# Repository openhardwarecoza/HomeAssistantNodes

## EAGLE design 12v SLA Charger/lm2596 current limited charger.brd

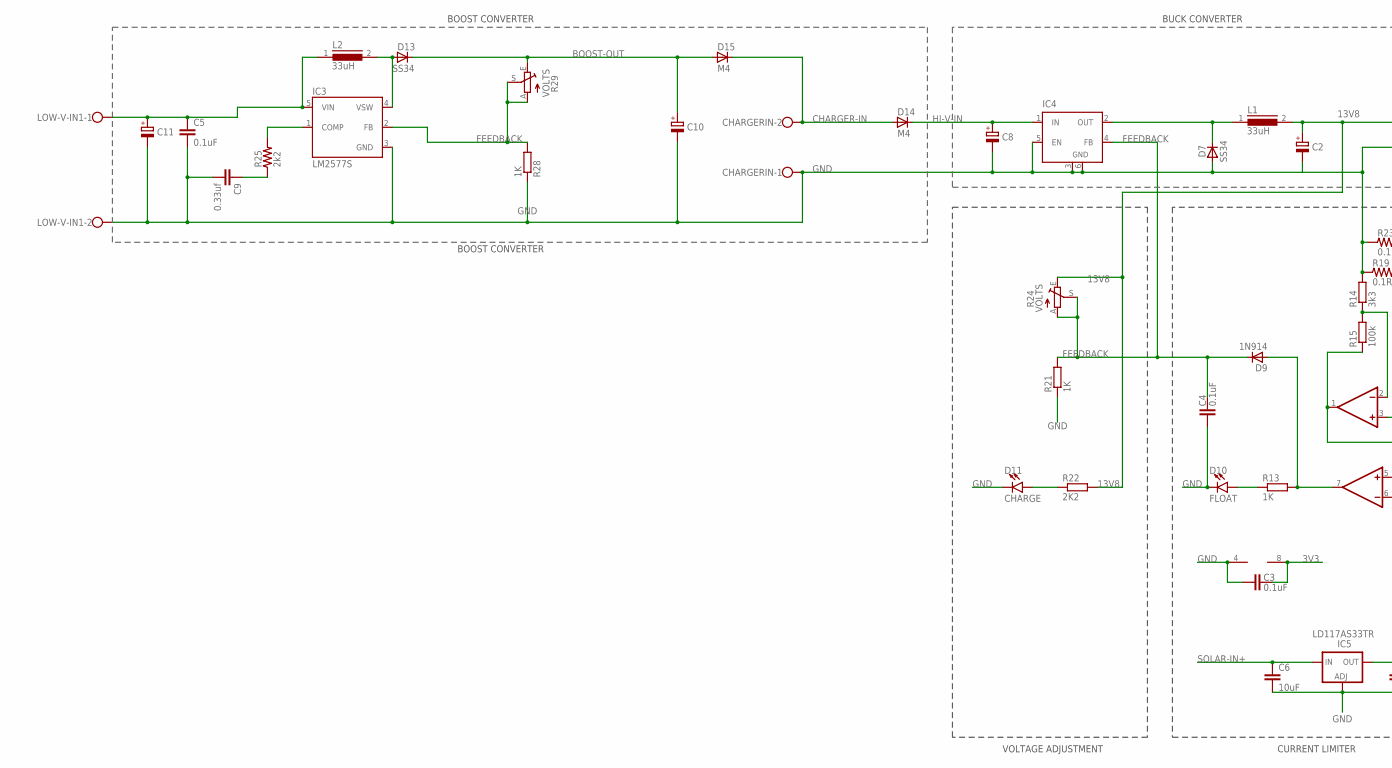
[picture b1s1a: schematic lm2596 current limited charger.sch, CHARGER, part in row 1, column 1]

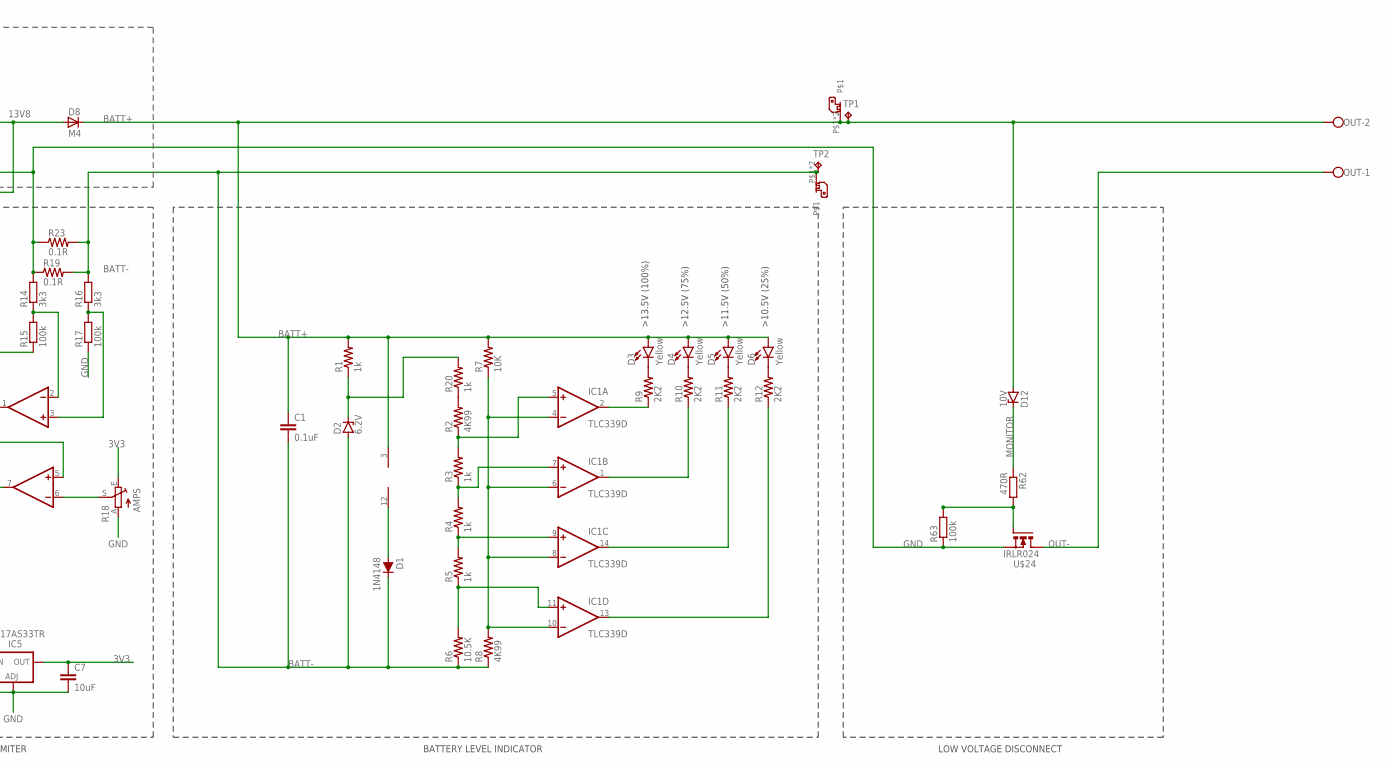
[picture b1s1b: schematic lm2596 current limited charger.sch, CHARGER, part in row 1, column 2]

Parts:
C1, C3, C4, C5: 0.1uF; C1206K
C2, C8, C10, C11: CPOL-EUE3.5-8; E3,5-8
C6, C7: 10uF; C1206K
C9: 0.33uf; C1206K
CHARGERIN: W237-102
D1: 1N4148; SOD-323
D2: 6.2V; SMB
D3, D4, D5, D6: Yellow; LED-1206
D7, D13: SS34; SOD87
D8, D14, D15: M4; SOD87
D9: 1N914; SOD87
D10: FLOAT; LED-1206
D11: CHARGE; LED-1206
D12: 10V; SMB
IC1: TLC339D; SO14
IC2: MCP602SN; SO08
IC3: LM2577S; TO263-5
IC4: LM2596S; TO263-5
IC5: LD117AS33TR; SOT223
L1, L2: 33uH; DR127
LOW-V-IN1: W237-102
OUT: W237-102
R1, R3, R4, R5, R20: 1k; R1206
R2, R8: 4K99; R1206
R6: 10.5K; R1206
R7: 10K; R1206
R9, R10, R11, R12, R22: 2K2; R1206
R13, R21, R28: 1K; R1206
R14, R16: 3k3; R1206
R15, R17: 100k; R1206
R18: AMPS; B64Y
R19, R23: 0.1R; R2512
R24, R29: VOLTS; B64Y
R25: 2k2; R2512
R62: 470R; R0603
R63: 100k; R0603
TP1, TP2: TPPAD1-20Y; P1-20Y
U$2, U$3: PCB-6.35MM-RA-SPADE
U$24: IRLR024; D-PAK_TO252AA

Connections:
3V3: C3.2, C7.1, IC2.8 (V+), IC5.4 (OUT), R18.E
13V8: C2.+, D8.2 (A), L1.2, R22.2, R24.E
BATT+: C1.1, D3.A, D4.A, D5.A, D6.A, D8.1 (C), D12.A, IC1.3 (V+), OUT.2, R1.2, R7.2, TP1.TP, U$2.P$1, U$2.P$2
BATT-: C1.2, D1.C, D2.A, R6.1, R8.1, R16.2, R19.2, R23.2, TP2.TP, U$3.P$1, U$3.P$2
BOOST-OUT: C10.+, D13.1 (C), D15.2 (A), R29.E
CHARGER-IN: CHARGERIN.2, D14.2 (A), D15.1 (C)
FEEDBACK: C4.2, D9.1 (C), IC3.2 (FB), IC4.4 (FB), R21.2, R24.A, R24.S, R28.2, R29.A, R29.S
GND: C2.-, C3.1, C4.1, C5.2, C6.2, C7.2, C8.-, C9.2, C10.-, C11.-, CHARGERIN.1, D7.2 (A), D10.C, D11.C, IC2.4 (V-), IC3.3 (GND), IC4.3 (GND), IC4.5 (EN), IC4.6 (GND), IC5.1 (ADJ), LOW-V-IN1.2, R14.2, R17.1, R18.A, R19.1, R21.1, R23.1, R28.1, R63.1, U$24.3 (S)
HI-V-IN: C8.+, D14.1 (C), IC4.1 (IN)
MONITOR: D12.C, R62.1
unnamed: D7.1 (C), IC4.2 (OUT), L1.1
unnamed: D2.C, R1.1, R20.2
unnamed: IC1.5 (+IN), R2.1, R3.2
unnamed: IC1.7 (+IN), R3.1, R4.2
unnamed: IC1.9 (+IN), R4.1, R5.2
unnamed: IC1.11 (+IN), R5.1, R6.2
unnamed: IC1.4 (-IN), IC1.6 (-IN), IC1.8 (-IN), IC1.10 (-IN), R7.1, R8.2
unnamed: D3.C, R9.2
unnamed: D4.C, R10.2
unnamed: D5.C, R11.2
unnamed: D6.C, R12.2
unnamed: R62.2, R63.2, U$24.1 (G)
unnamed: IC1.2 (OUT), R9.1
unnamed: IC1.1 (OUT), R10.1
unnamed: IC1.14 (OUT), R11.1
unnamed: IC1.13 (OUT), R12.1
unnamed: D1.A, IC1.12 (V-)
unnamed: D9.2 (A), IC2.7 (OUT), R13.2
unnamed: IC2.6 (-IN), R18.S
unnamed: D10.A, R13.1
unnamed: IC2.1 (OUT), IC2.5 (+IN), R15.1
unnamed: D11.A, R22.1
unnamed: IC2.3 (+IN), R16.1, R17.2
unnamed: IC2.2 (-IN), R14.1, R15.2
unnamed: R2.2, R20.1
unnamed: C5.1, C11.+, IC3.5 (VIN), L2.1, LOW-V-IN1.1
unnamed: IC3.1 (COMP), R25.2
unnamed: C9.1, R25.1
unnamed: D13.2 (A), IC3.4 (VSW), L2.2
OUT-: OUT.1, U$24.4 (D)
SOLAR-IN+: C6.1, IC5.3 (IN)

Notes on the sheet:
CURRENT LIMITER
VOLTAGE ADJUSTMENT
LOW VOLTAGE DISCONNECT
BATTERY LEVEL INDICATOR
BOOST CONVERTER
BUCK CONVERTER

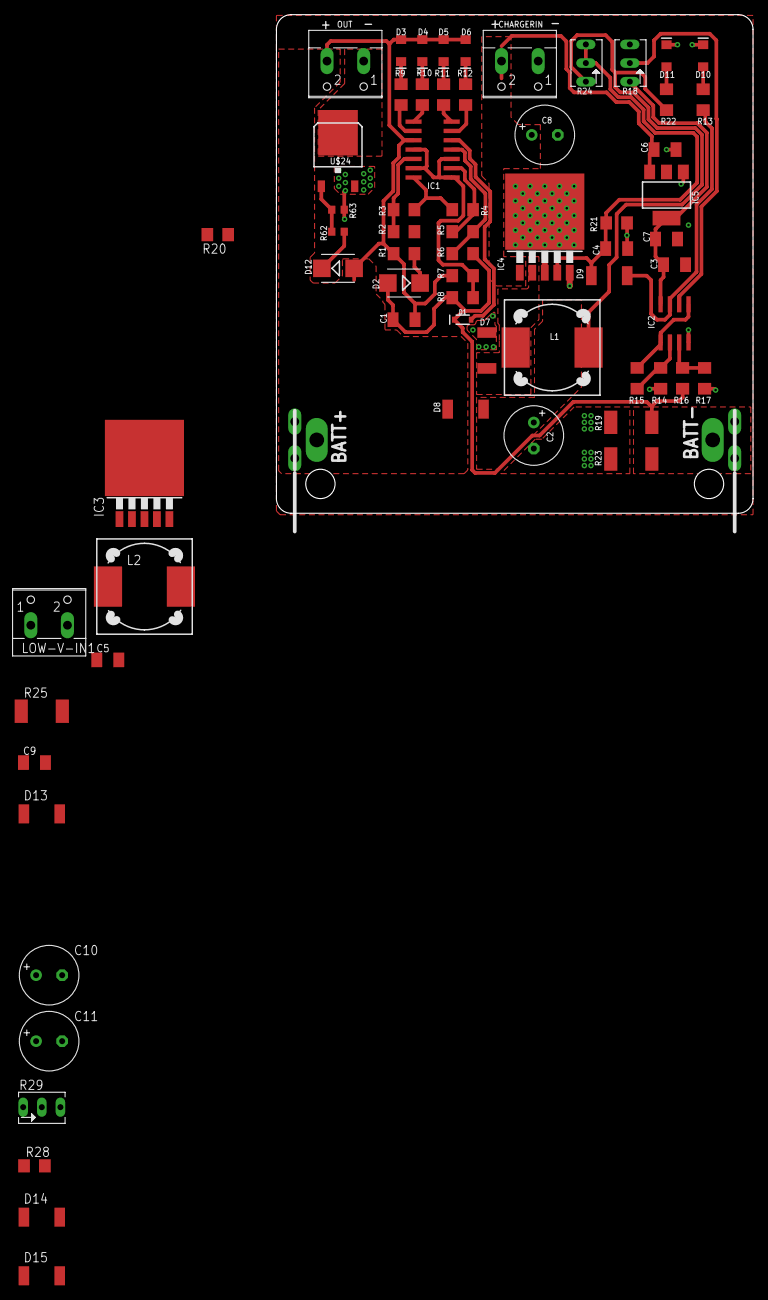
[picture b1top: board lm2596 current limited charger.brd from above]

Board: 2 copper layers, 65.0 x 68.0 mm, 70 parts (0 on the bottom side), 41 nets.

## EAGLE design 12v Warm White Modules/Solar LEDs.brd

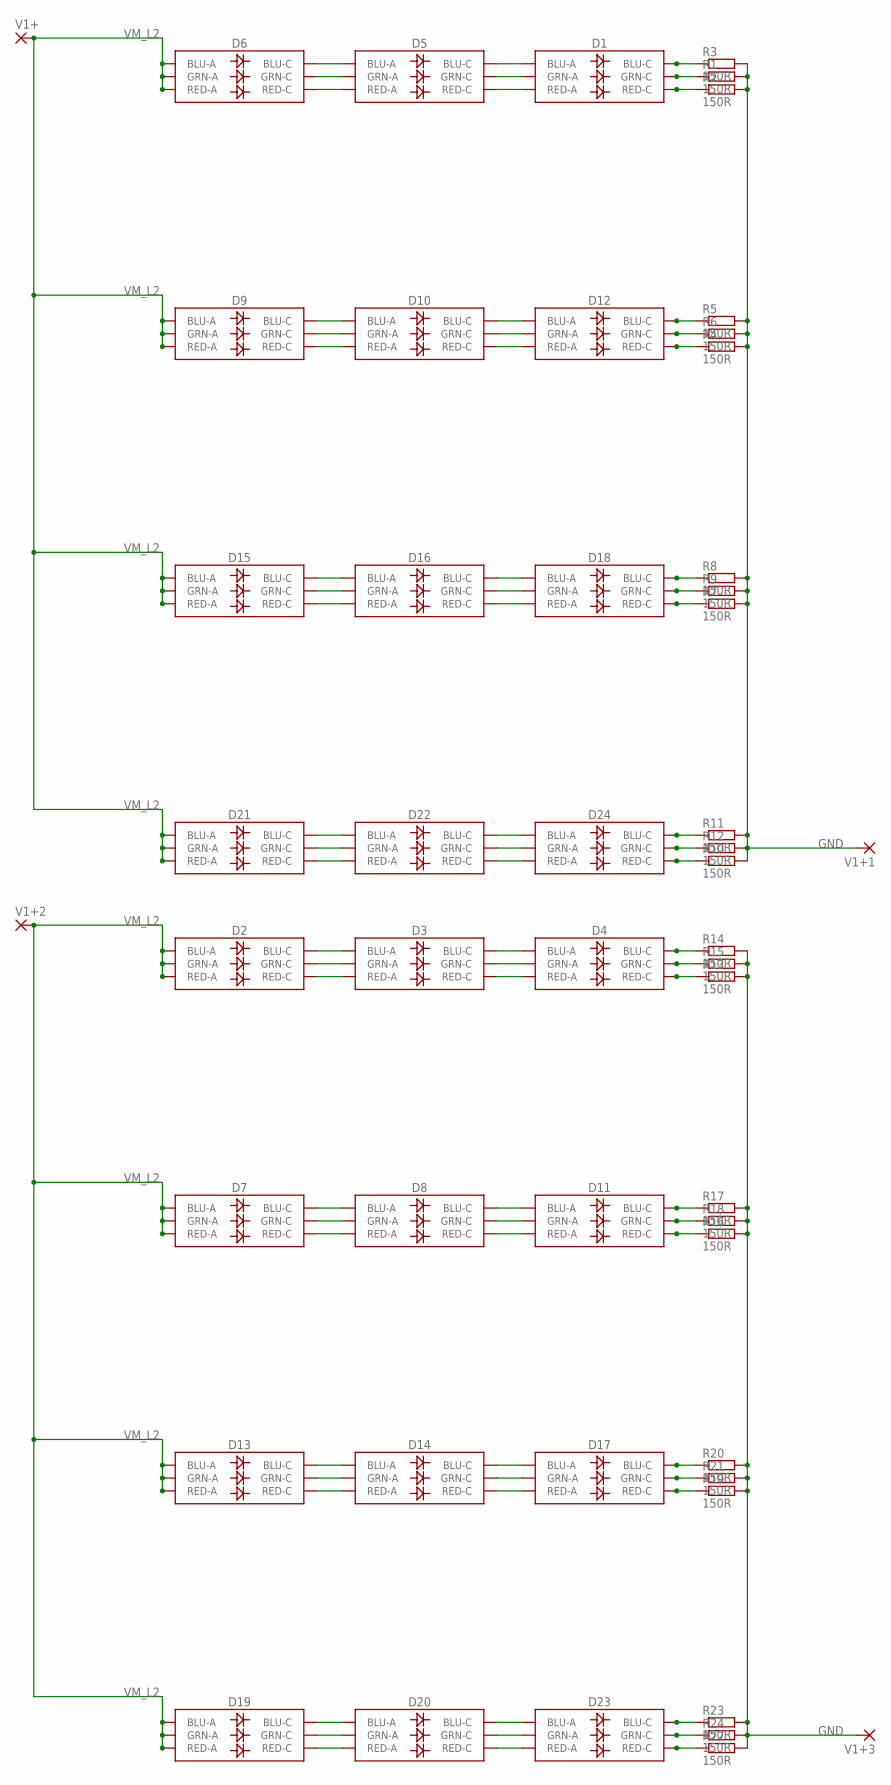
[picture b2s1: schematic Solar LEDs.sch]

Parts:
D1, D2, D3, D4, D5, D6, D7, D8, D9, D10, D11, D12, D13, D14, D15, D16, D17, D18, D19, D20, D21, D22, D23, D24: LED-RGBNO_IC; LED-TRICOLOR-5050
R1, R2, R3, R4, R5, R6, R7, R8, R9, R10, R11, R12, R13, R14, R15, R16, R17, R18, R19, R20, R21, R22, R23, R24: 150R; M1206
V1+, V1+1, V1+2, V1+3: 2,54/1,0

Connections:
GND: R1.2, R2.2, R3.2, R4.2, R5.2, R6.2, R7.2, R8.2, R9.2, R10.2, R11.2, R12.2, R13.2, R14.2, R15.2, R16.2, R17.2, R18.2, R19.2, R20.2, R21.2, R22.2, R23.2, R24.2, V1+1.1, V1+3.1
unnamed: D2.4 (BLU-C), D3.3 (BLU-A)
unnamed: D9.4 (BLU-C), D10.3 (BLU-A)
unnamed: D9.6 (GRN-C), D10.1 (GRN-A)
unnamed: D9.5 (RED-C), D10.2 (RED-A)
unnamed: D2.6 (GRN-C), D3.1 (GRN-A)
unnamed: D2.5 (RED-C), D3.2 (RED-A)
unnamed: D3.4 (BLU-C), D4.3 (BLU-A)
unnamed: D3.6 (GRN-C), D4.1 (GRN-A)
unnamed: D3.5 (RED-C), D4.2 (RED-A)
unnamed: D4.4 (BLU-C), R14.1
unnamed: D4.6 (GRN-C), R15.1
unnamed: D4.5 (RED-C), R13.1
unnamed: D7.4 (BLU-C), D8.3 (BLU-A)
unnamed: D10.4 (BLU-C), D12.3 (BLU-A)
unnamed: D10.6 (GRN-C), D12.1 (GRN-A)
unnamed: D10.5 (RED-C), D12.2 (RED-A)
unnamed: D12.4 (BLU-C), R5.1
unnamed: D12.6 (GRN-C), R6.1
unnamed: D5.3 (BLU-A), D6.4 (BLU-C)
unnamed: D5.1 (GRN-A), D6.6 (GRN-C)
unnamed: D5.2 (RED-A), D6.5 (RED-C)
unnamed: D7.6 (GRN-C), D8.1 (GRN-A)
unnamed: D7.5 (RED-C), D8.2 (RED-A)
unnamed: D8.4 (BLU-C), D11.3 (BLU-A)
unnamed: D8.6 (GRN-C), D11.1 (GRN-A)
unnamed: D8.5 (RED-C), D11.2 (RED-A)
unnamed: D11.4 (BLU-C), R17.1
unnamed: D11.6 (GRN-C), R18.1
unnamed: D11.5 (RED-C), R16.1
unnamed: D13.4 (BLU-C), D14.3 (BLU-A)
unnamed: D1.3 (BLU-A), D5.4 (BLU-C)
unnamed: D1.1 (GRN-A), D5.6 (GRN-C)
unnamed: D1.2 (RED-A), D5.5 (RED-C)
unnamed: D12.5 (RED-C), R4.1
unnamed: D15.4 (BLU-C), D16.3 (BLU-A)
unnamed: D15.6 (GRN-C), D16.1 (GRN-A)
unnamed: D15.5 (RED-C), D16.2 (RED-A)
unnamed: D13.6 (GRN-C), D14.1 (GRN-A)
unnamed: D13.5 (RED-C), D14.2 (RED-A)
unnamed: D14.4 (BLU-C), D17.3 (BLU-A)
unnamed: D14.6 (GRN-C), D17.1 (GRN-A)
unnamed: D14.5 (RED-C), D17.2 (RED-A)
unnamed: D1.4 (BLU-C), R3.1
unnamed: D1.6 (GRN-C), R1.1
unnamed: D1.5 (RED-C), R2.1
unnamed: D17.4 (BLU-C), R20.1
unnamed: D17.6 (GRN-C), R21.1
unnamed: D17.5 (RED-C), R19.1
unnamed: D19.4 (BLU-C), D20.3 (BLU-A)
unnamed: D16.4 (BLU-C), D18.3 (BLU-A)
unnamed: D16.6 (GRN-C), D18.1 (GRN-A)
unnamed: D16.5 (RED-C), D18.2 (RED-A)
unnamed: D18.4 (BLU-C), R8.1
unnamed: D18.6 (GRN-C), R9.1
unnamed: D18.5 (RED-C), R7.1
unnamed: D21.4 (BLU-C), D22.3 (BLU-A)
unnamed: D21.6 (GRN-C), D22.1 (GRN-A)
unnamed: D21.5 (RED-C), D22.2 (RED-A)
unnamed: D19.6 (GRN-C), D20.1 (GRN-A)
unnamed: D19.5 (RED-C), D20.2 (RED-A)
unnamed: D20.4 (BLU-C), D23.3 (BLU-A)
unnamed: D20.6 (GRN-C), D23.1 (GRN-A)
unnamed: D20.5 (RED-C), D23.2 (RED-A)
unnamed: D23.4 (BLU-C), R23.1
unnamed: D23.6 (GRN-C), R24.1
unnamed: D23.5 (RED-C), R22.1
unnamed: D22.4 (BLU-C), D24.3 (BLU-A)
unnamed: D22.6 (GRN-C), D24.1 (GRN-A)
unnamed: D22.5 (RED-C), D24.2 (RED-A)
unnamed: D24.4 (BLU-C), R11.1
unnamed: D24.6 (GRN-C), R12.1
unnamed: D24.5 (RED-C), R10.1
VM_L2: D2.1 (GRN-A), D2.2 (RED-A), D2.3 (BLU-A), D6.1 (GRN-A), D6.2 (RED-A), D6.3 (BLU-A), D7.1 (GRN-A), D7.2 (RED-A), D7.3 (BLU-A), D9.1 (GRN-A), D9.2 (RED-A), D9.3 (BLU-A), D13.1 (GRN-A), D13.2 (RED-A), D13.3 (BLU-A), D15.1 (GRN-A), D15.2 (RED-A), D15.3 (BLU-A), D19.1 (GRN-A), D19.2 (RED-A), D19.3 (BLU-A), D21.1 (GRN-A), D21.2 (RED-A), D21.3 (BLU-A), V1+.1, V1+2.1

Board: 2 copper layers, 52 parts (0 on the bottom side), 74 nets, no tracks yet.

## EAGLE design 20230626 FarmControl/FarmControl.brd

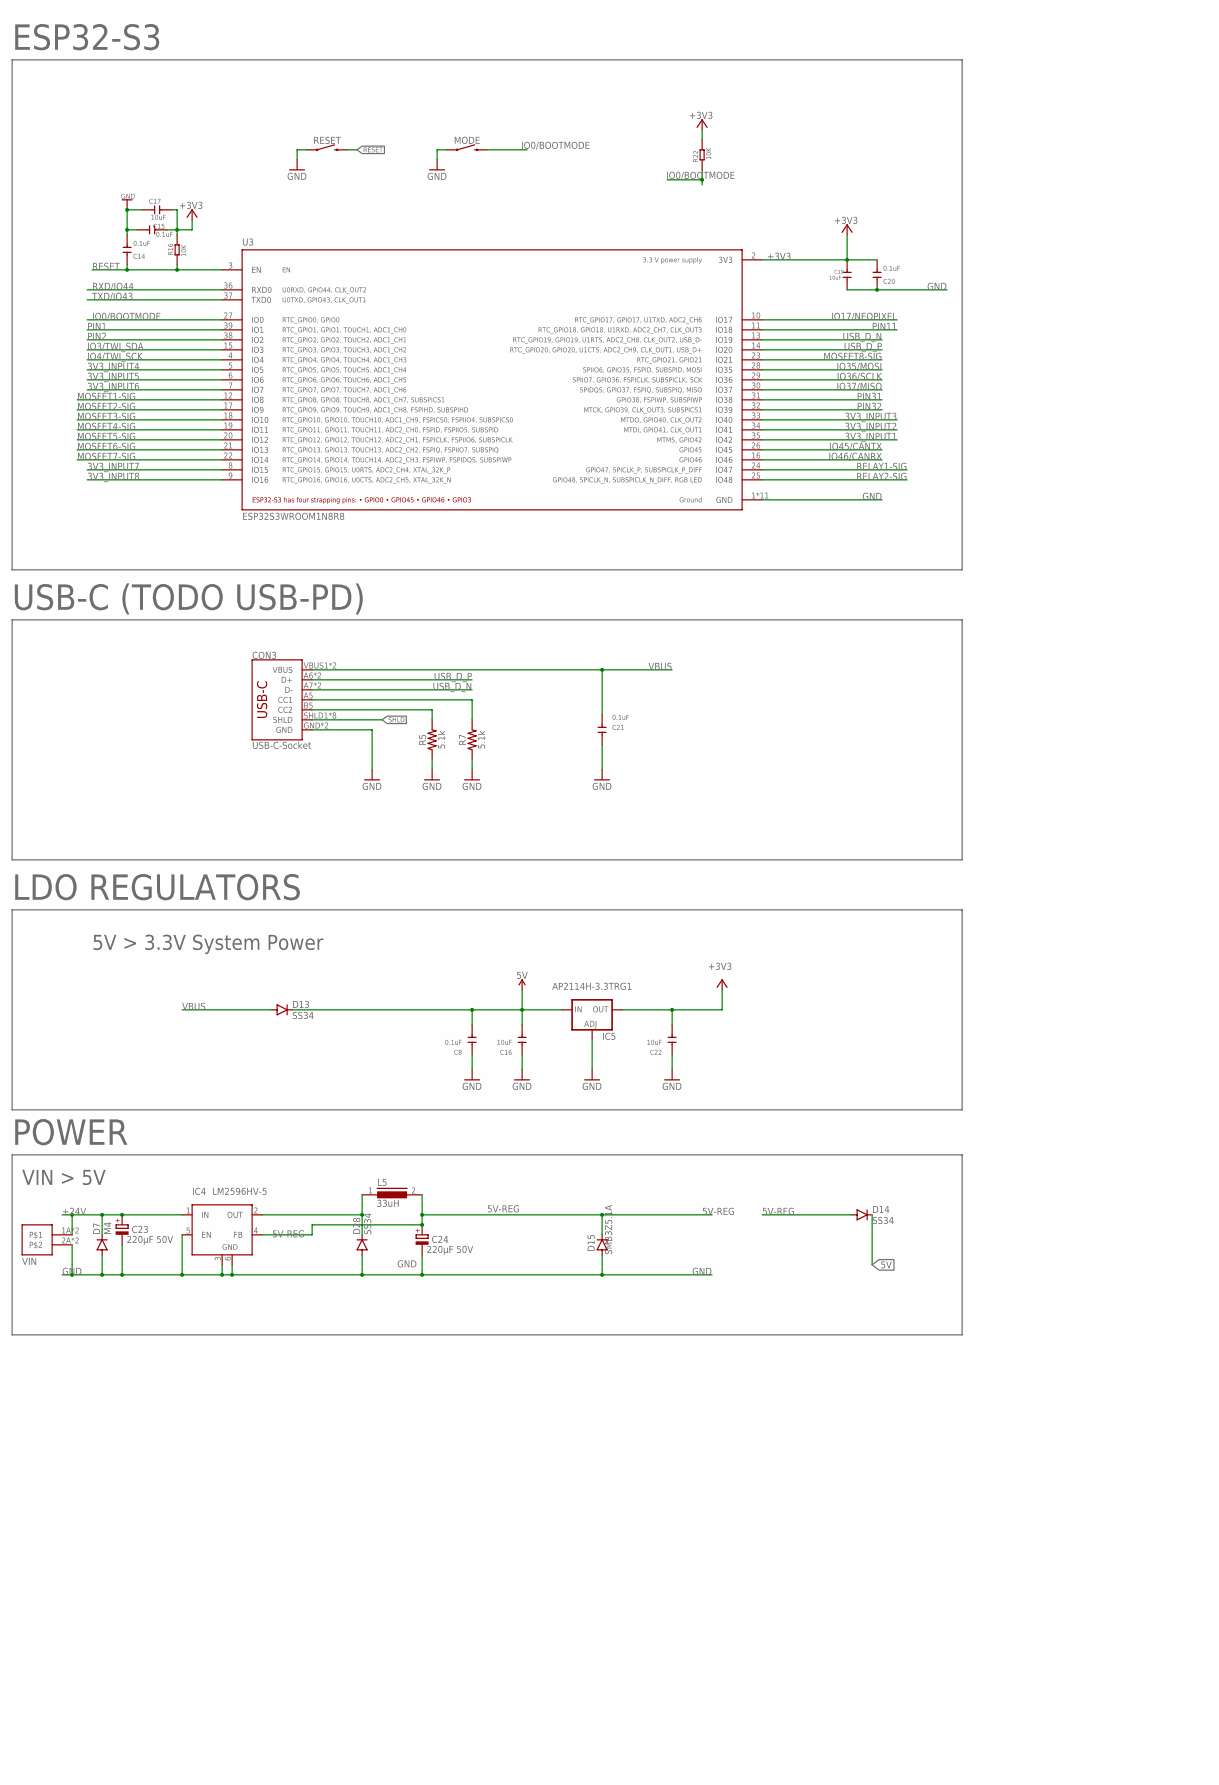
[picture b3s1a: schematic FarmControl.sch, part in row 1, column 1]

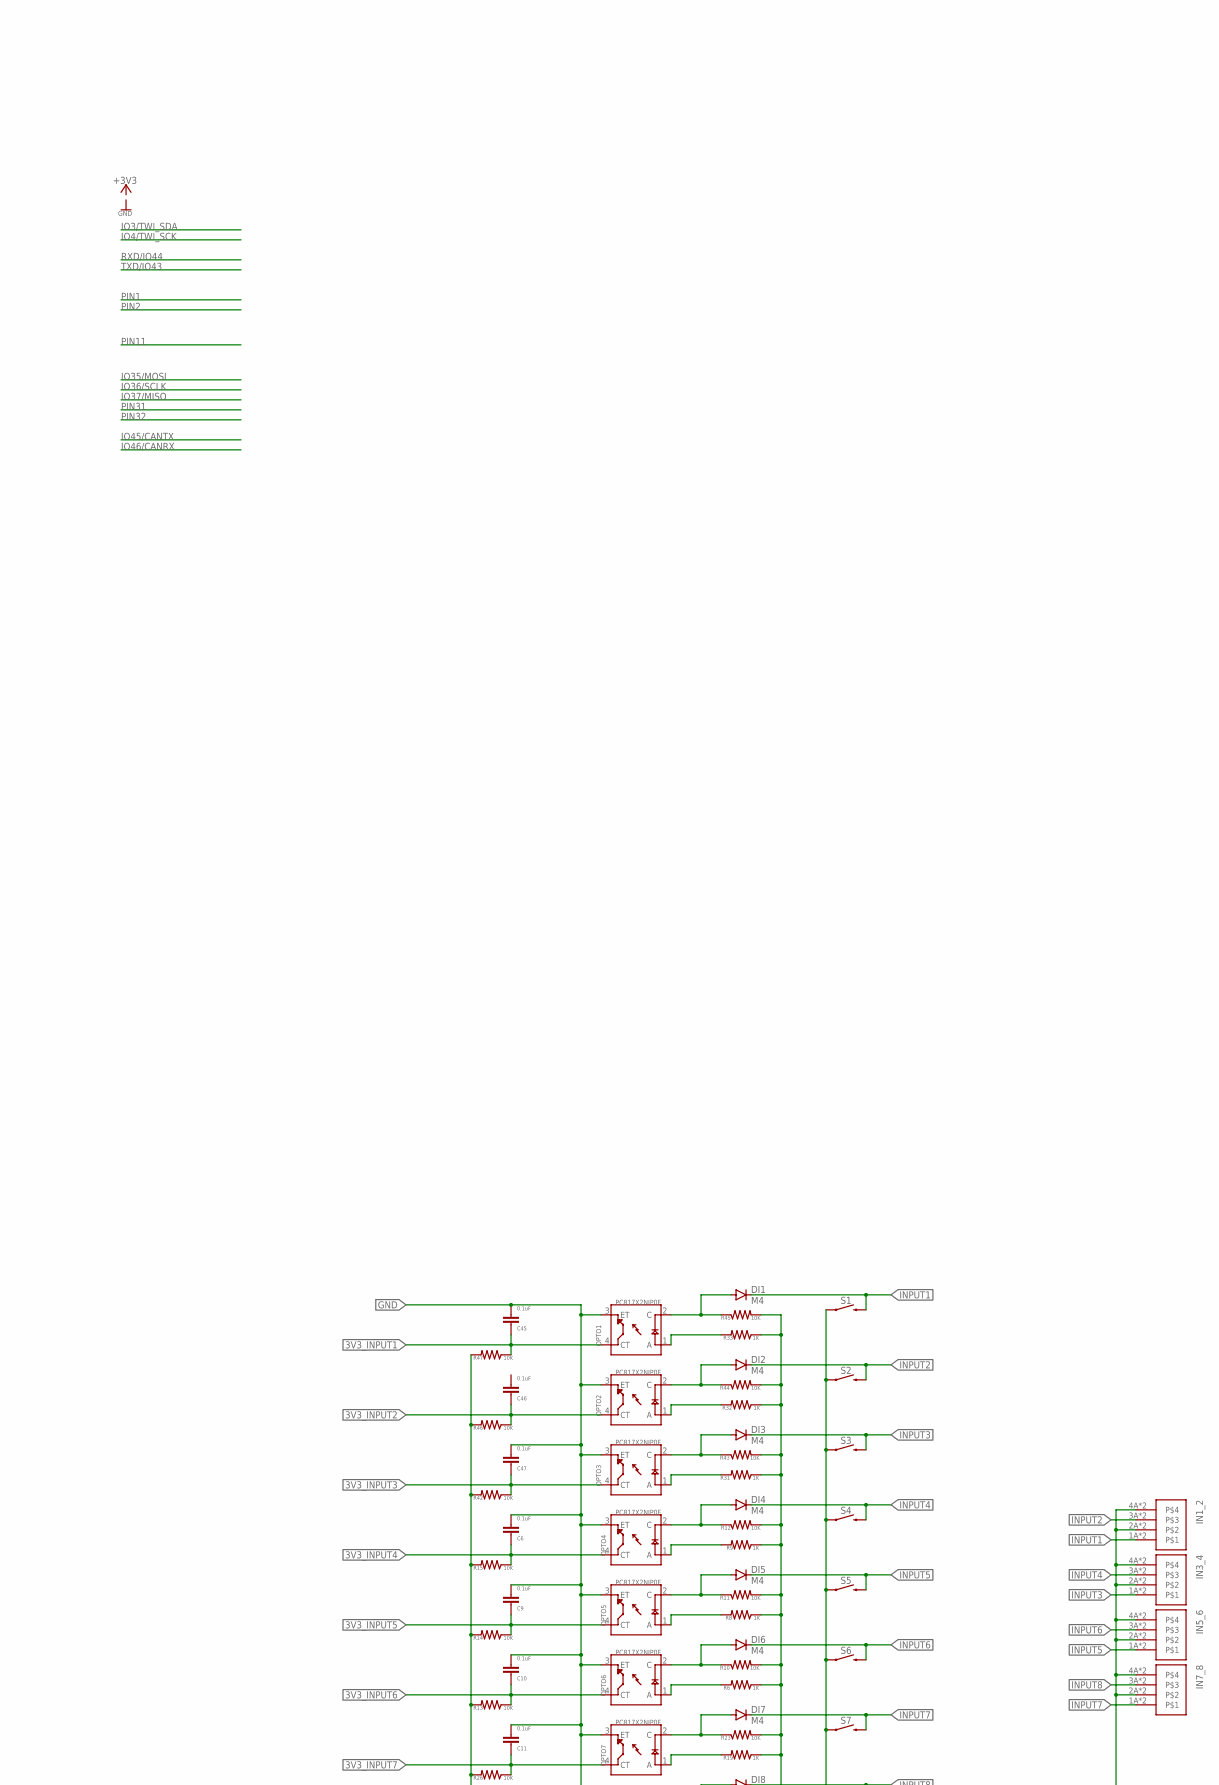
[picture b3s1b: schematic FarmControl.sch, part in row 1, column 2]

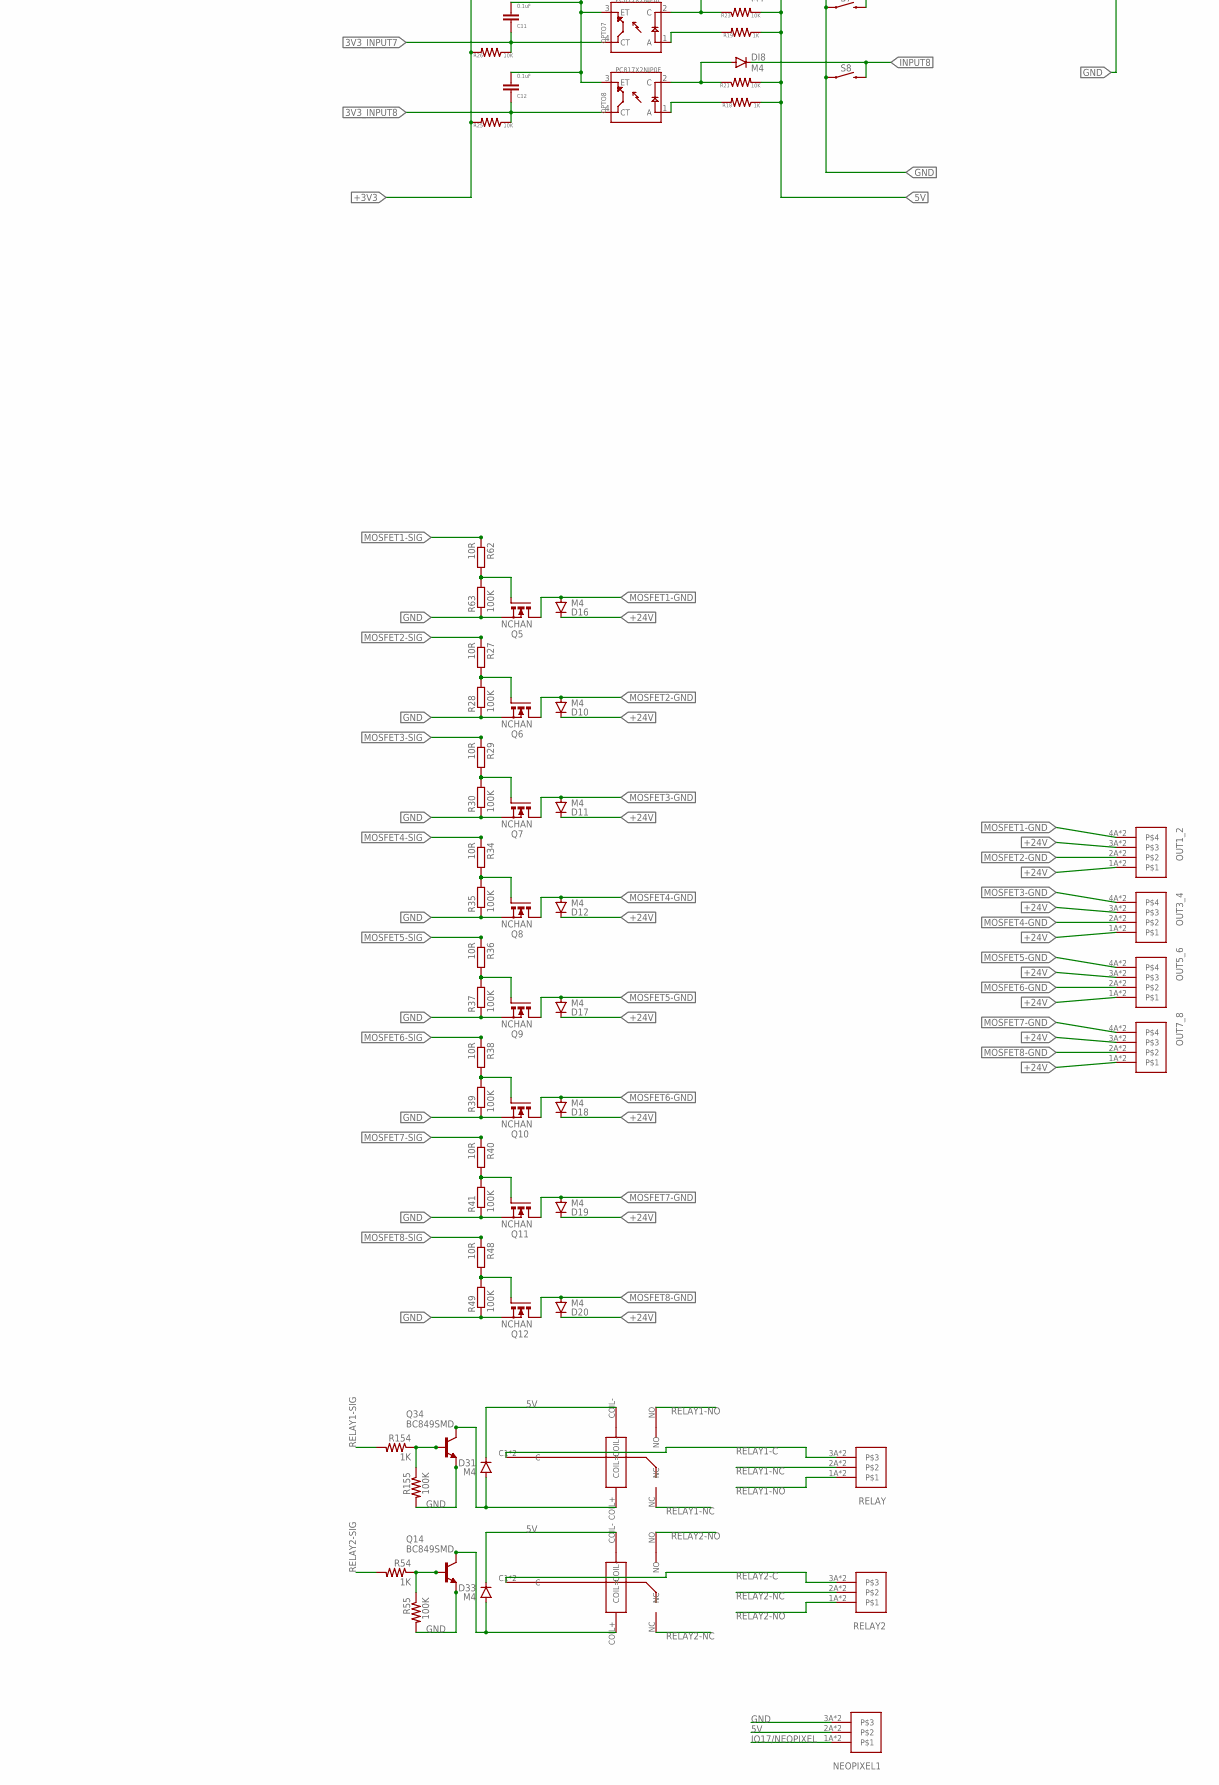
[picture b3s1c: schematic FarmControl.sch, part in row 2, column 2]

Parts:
C6, C9, C10, C11, C12, C45, C46, C47: 0.1uF; C1206
C8, C14, C15, C20, C21: 0.1uF; DISCRETE_C1206
C16, C19, C22: 10uF; C1206
C17: 10uF; DISCRETE_C1206
C23, C24: 220µF 50V; PANASONIC_E
CON3: USB-C-Socket; USB-C-16P
D7, D10, D11, D12, D16, D17, D18, D19, D20, D31, D33: M4; DO-214AC
D13: SS34; DO-214AC
D14, D28: SS34; SMB
D15: SMB3Z5.1A; SMB
DI1, DI2, DI3, DI4, DI5, DI6, DI7, DI8: M4; DO-214AC
IC4: LM2596HV-5; TO263-5
IC5: AP2114H-3.3TRG1; SOT223
IN1_2, IN3_4, IN5_6, IN7_8: WJ212R-THR-3.5-4
L5: 33uH; DR127
MODE: MOMENTARY-SWITCH-SPST-PTH-6.0MM; TACTILE_SWITCH_PTH_6.0MM
NEOPIXEL1: WJ212R-THR-3.5-3
OPTO1, OPTO2, OPTO3, OPTO4, OPTO5, OPTO6, OPTO7, OPTO8: PC817X2NIP0F; SOT254P975X400-4N
OUT1_2, OUT3_4, OUT5_6, OUT7_8: WJ212R-THR-3.5-4
Q5, Q6, Q7, Q8, Q9, Q10, Q11, Q12: NCHAN; D-PAK_TO252AA
Q14, Q34: BC849SMD; SOT23-BEC
R5, R7: 5.1k; 0603@1
R6, R8, R9, R18, R19, R31, R32, R33, R54, R154: 1K; R1206
R10, R11, R12, R13, R14, R15, R16, R21, R22, R23, R25, R26, R42, R43, R44, R45, R46, R47: 10K; R1206
R27, R29, R34, R36, R38, R40, R48, R62: 10R; R1206
R28, R30, R35, R37, R39, R41, R49, R55, R63, R155: 100K; R1206
RELAY, RELAY2: WJ212R-THR-3.5-3
RESET: MOMENTARY-SWITCH-SPST-PTH-6.0MM; TACTILE_SWITCH_PTH_6.0MM
S1, S2, S3, S4, S5, S6, S7, S8: MOMENTARY-SWITCH-SPST-PTH-6.0MM; TACTILE_SWITCH_PTH_6.0MM
U3: ESP32S3WROOM1N8R8; XCVR_ESP32S3WROOM1N8R8
U$1, U$3: JRC-21F-4100
VIN: WJ212R-THR-3.5-2

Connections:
3V3_INPUT1: C45.1, OPTO1.4 (CT), R47.1, U3.35 (IO42)
3V3_INPUT2: C46.1, OPTO2.4 (CT), R46.1, U3.34 (IO41)
3V3_INPUT3: C47.1, OPTO3.4 (CT), R42.1, U3.33 (IO40)
3V3_INPUT4: C6.1, OPTO4.4 (CT), R15.1, U3.5 (IO5)
3V3_INPUT5: C9.1, OPTO5.4 (CT), R14.1, U3.6 (IO6)
3V3_INPUT6: C10.1, OPTO6.4 (CT), R13.1, U3.7 (IO7)
3V3_INPUT7: C11.1, OPTO7.4 (CT), R26.1, U3.8 (IO15)
3V3_INPUT8: C12.1, OPTO8.4 (CT), R25.1, U3.9 (IO16)
5V: C8.2, C16.1, D13.C, D14.C, D31.C, D33.C, IC5.3 (IN), NEOPIXEL1.2A, NEOPIXEL1.2B, R6.1, R8.1, R9.1, R10.2, R11.2, R12.2, R18.1, R19.1, R21.2, R23.2, R31.1, R32.1, R33.1, R43.2, R44.2, R45.2, U$1.COIL-, U$3.COIL-
5V-REG: C24.+, D14.A, D15.C, IC4.4 (FB), L5.2
+3V3: C15.1, C17.1, C19.1, C20.2, C22.1, IC5.4 (OUT), R13.2, R14.2, R15.2, R16.2, R22.2, R25.2, R26.2, R42.2, R46.2, R47.2, U3.2 (3V3)
+24V: C23.+, D7.C, D10.C, D11.C, D12.C, D16.C, D17.C, D18.C, D19.C, D20.C, IC4.1 (IN), OUT1_2.1A, OUT1_2.1B, OUT1_2.3A, OUT1_2.3B, OUT3_4.1A, OUT3_4.1B, OUT3_4.3A, OUT3_4.3B, OUT5_6.1A, OUT5_6.1B, OUT5_6.3A, OUT5_6.3B, OUT7_8.1A, OUT7_8.1B, OUT7_8.3A, OUT7_8.3B, VIN.1A, VIN.1B
CC1: CON3.A5 (CC1), R7.2
CC2: CON3.B5 (CC2), R5.2
COIL-1: D31.A, Q34.C, U$3.COIL+ (COIL=)
COIL-2: D33.A, Q14.C, U$1.COIL+ (COIL=)
GND: C6.2, C8.1, C9.2, C10.2, C11.2, C12.2, C14.2, C15.2, C16.2, C17.2, C19.2, C20.1, C21.1, C22.2, C23.-, C24.-, C45.2, C47.2, CON3.GND, CON3.GND2 (GND), D7.A, D15.A, D28.A, IC4.3 (GND), IC4.5 (EN), IC4.6 (GND), IC5.1 (ADJ), IN1_2.2A, IN1_2.2B, IN1_2.4A, IN1_2.4B, IN3_4.2A, IN3_4.2B, IN3_4.4A, IN3_4.4B, IN5_6.2A, IN5_6.2B, IN5_6.4A, IN5_6.4B, IN7_8.2A, IN7_8.2B, IN7_8.4A, IN7_8.4B, MODE.1, NEOPIXEL1.3A, NEOPIXEL1.3B, OPTO1.3 (ET), OPTO2.3 (ET), OPTO3.3 (ET), OPTO4.3 (ET), OPTO5.3 (ET), OPTO6.3 (ET), OPTO7.3 (ET), OPTO8.3 (ET), Q5.3 (S), Q6.3 (S), Q7.3 (S), Q8.3 (S), Q9.3 (S), Q10.3 (S), Q11.3 (S), Q12.3 (S), Q14.E, Q34.E, R5.1, R7.1, R28.1, R30.1, R35.1, R37.1, R39.1, R41.1, R49.1, R55.2, R63.1, R155.2, RESET.1, S1.1, S2.1, S3.1, S4.1, S5.1, S6.1, S7.1, S8.1, U3.1 (GND), U3.40 (GND), U3.41_1 (GND), U3.41_2 (GND), U3.41_3 (GND), U3.41_4 (GND), U3.41_5 (GND), U3.41_6 (GND), U3.41_7 (GND), U3.41_8 (GND), U3.41_9 (GND), VIN.2A, VIN.2B
INPUT1: DI1.C, IN1_2.1A, IN1_2.1B, S1.3 (2)
INPUT2: DI2.C, IN1_2.3A, IN1_2.3B, S2.3 (2)
INPUT3: DI3.C, IN3_4.1A, IN3_4.1B, S3.3 (2)
INPUT4: DI4.C, IN3_4.3A, IN3_4.3B, S4.3 (2)
INPUT5: DI5.C, IN5_6.1A, IN5_6.1B, S5.3 (2)
INPUT6: DI6.C, IN5_6.3A, IN5_6.3B, S6.3 (2)
INPUT7: DI7.C, IN7_8.1A, IN7_8.1B, S7.3 (2)
INPUT8: DI8.C, IN7_8.3A, IN7_8.3B, S8.3 (2)
IO0/BOOTMODE: MODE.3 (2), R22.1, U3.27 (IO0)
IO3/TWI_SDA: U3.15 (IO3)
IO4/TWI_SCK: U3.4 (IO4)
IO17/NEOPIXEL: NEOPIXEL1.1A, NEOPIXEL1.1B, U3.10 (IO17)
IO35/MOSI: U3.28 (IO35)
IO36/SCLK: U3.29 (IO36)
IO37/MISO: U3.30 (IO37)
IO45/CANTX: U3.26 (IO45)
IO46/CANRX: U3.16 (IO46)
MOSFET1-GND: D16.A, OUT1_2.4A, OUT1_2.4B, Q5.4 (D)
MOSFET1-SIG: R62.1, U3.12 (IO8)
MOSFET2-GND: D10.A, OUT1_2.2A, OUT1_2.2B, Q6.4 (D)
MOSFET2-SIG: R27.1, U3.17 (IO9)
MOSFET3-GND: D11.A, OUT3_4.4A, OUT3_4.4B, Q7.4 (D)
MOSFET3-SIG: R29.1, U3.18 (IO10)
MOSFET4-GND: D12.A, OUT3_4.2A, OUT3_4.2B, Q8.4 (D)
MOSFET4-SIG: R34.1, U3.19 (IO11)
MOSFET5-GND: D17.A, OUT5_6.4A, OUT5_6.4B, Q9.4 (D)
MOSFET5-SIG: R36.1, U3.20 (IO12)
MOSFET6-GND: D18.A, OUT5_6.2A, OUT5_6.2B, Q10.4 (D)
MOSFET6-SIG: R38.1, U3.21 (IO13)
MOSFET7-GND: D19.A, OUT7_8.4A, OUT7_8.4B, Q11.4 (D)
MOSFET7-SIG: R40.1, U3.22 (IO14)
MOSFET8-GND: D20.A, OUT7_8.2A, OUT7_8.2B, Q12.4 (D)
MOSFET8-SIG: R48.1, U3.23 (IO21)
unnamed: OPTO6.1 (A), R6.2
unnamed: OPTO5.1 (A), R8.2
unnamed: OPTO4.1 (A), R9.2
unnamed: DI4.A, OPTO4.2 (C), R12.1
unnamed: Q5.1 (G), R62.2, R63.2
unnamed: DI5.A, OPTO5.2 (C), R11.1
unnamed: DI6.A, OPTO6.2 (C), R10.1
unnamed: OPTO8.1 (A), R18.2
unnamed: OPTO7.1 (A), R19.2
unnamed: DI7.A, OPTO7.2 (C), R23.1
unnamed: DI8.A, OPTO8.2 (C), R21.1
unnamed: Q6.1 (G), R27.2, R28.2
unnamed: Q7.1 (G), R29.2, R30.2
unnamed: Q8.1 (G), R34.2, R35.2
unnamed: Q9.1 (G), R36.2, R37.2
unnamed: Q10.1 (G), R38.2, R39.2
unnamed: Q11.1 (G), R40.2, R41.2
unnamed: Q12.1 (G), R48.2, R49.2
unnamed: Q14.B, R54.1, R55.1
unnamed: Q34.B, R154.1, R155.1
unnamed: OPTO3.1 (A), R31.2
unnamed: OPTO2.1 (A), R32.2
unnamed: OPTO1.1 (A), R33.2
unnamed: DI1.A, OPTO1.2 (C), R45.1
unnamed: DI2.A, OPTO2.2 (C), R44.1
unnamed: DI3.A, OPTO3.2 (C), R43.1
unnamed: D28.C, IC4.2 (OUT), L5.1
PIN1: U3.39 (IO1)
PIN2: U3.38 (IO2)
PIN11: U3.11 (IO18)
PIN31: U3.31 (IO38)
PIN32: U3.32 (IO39)
RELAY1-C: RELAY.3A, RELAY.3B, U$3.C1 (C), U$3.C2 (C)
RELAY1-NC: RELAY.2A, RELAY.2B, U$3.NC
RELAY1-NO: RELAY.1A, RELAY.1B, U$3.NO
RELAY1-SIG: R154.2, U3.24 (IO47)
RELAY2-C: RELAY2.3A, RELAY2.3B, U$1.C1 (C), U$1.C2 (C)
RELAY2-NC: RELAY2.2A, RELAY2.2B, U$1.NC
RELAY2-NO: RELAY2.1A, RELAY2.1B, U$1.NO
RELAY2-SIG: R54.2, U3.25 (IO48)
RESET: C14.1, R16.1, RESET.3 (2), U3.3 (EN)
RXD/IO44: U3.36 (RXD0)
SHLD: CON3.SHLD1 (SHLD), CON3.SHLD2 (SHLD), CON3.SHLD3 (SHLD), CON3.SHLD4 (SHLD), CON3.SHLD5 (SHLD), CON3.SHLD6 (SHLD), CON3.SHLD7 (SHLD), CON3.SHLD8 (SHLD)
TXD/IO43: U3.37 (TXD0)
USB_D_N: CON3.A7 (D-), CON3.B7 (D-), U3.13 (IO19)
USB_D_P: CON3.A6 (D+), CON3.B6 (D+), U3.14 (IO20)
VBUS: C21.2, CON3.VBUS1 (VBUS), CON3.VBUS2 (VBUS), D13.A

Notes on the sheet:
ESP32-S3
5V > 3.3V System Power
USB-C (TODO USB-PD)
LDO REGULATORS
POWER
VIN > 5V

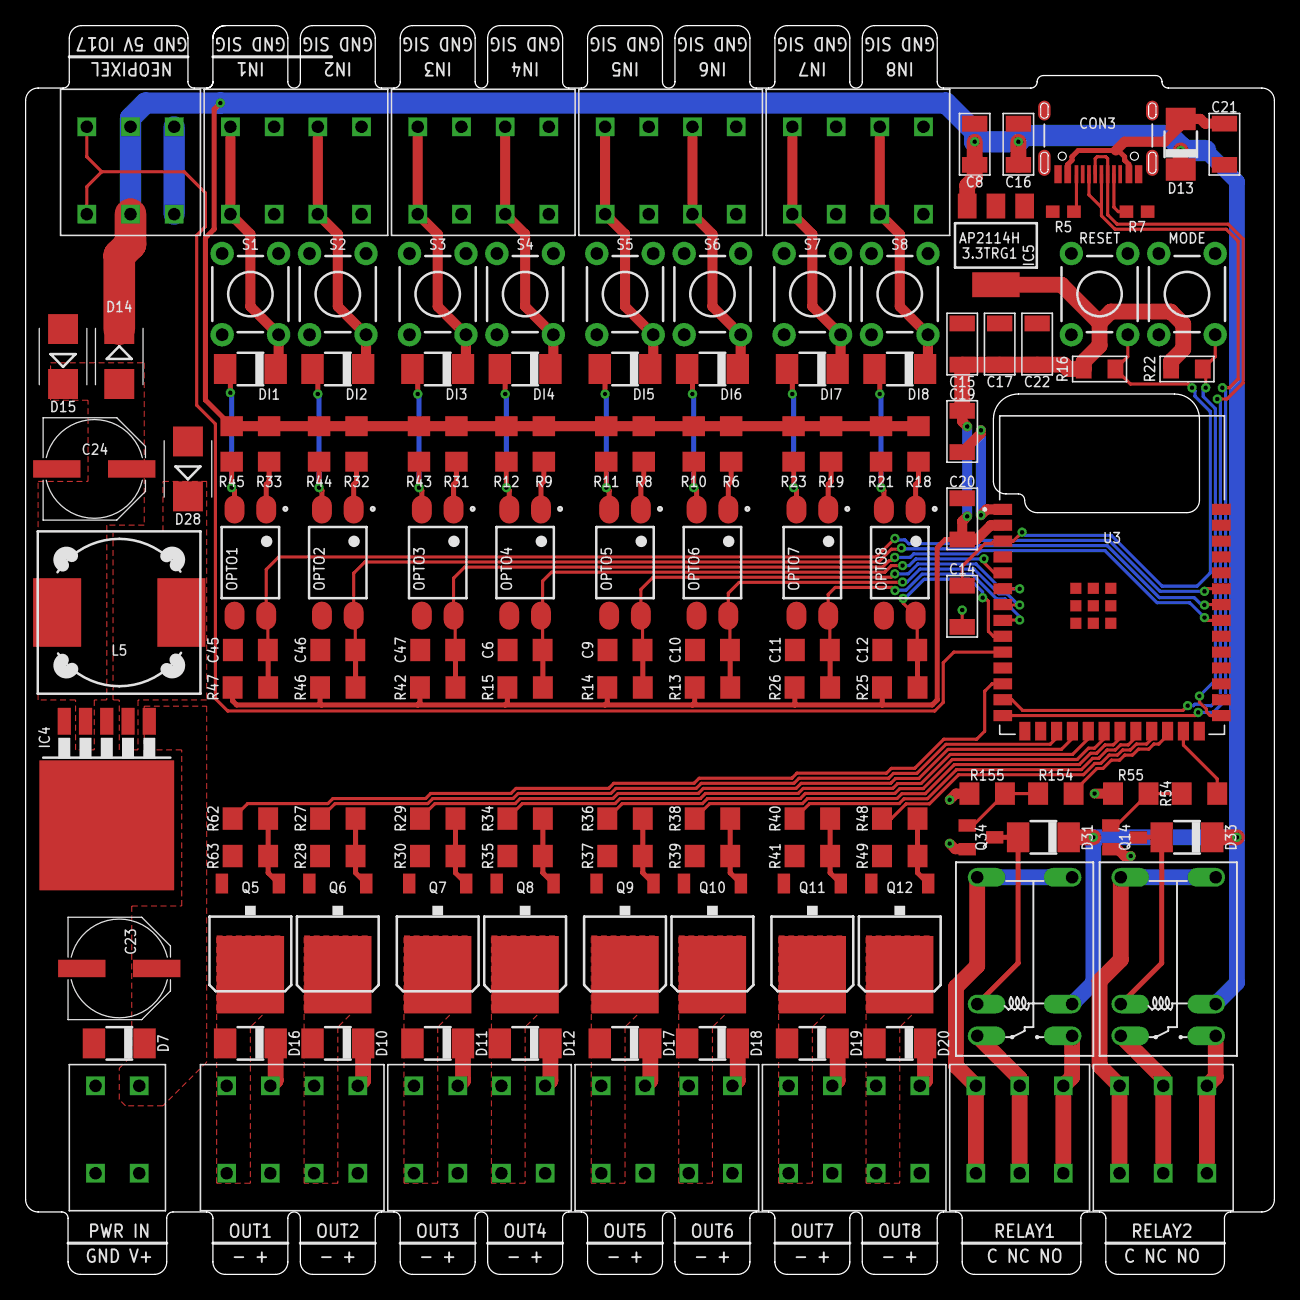
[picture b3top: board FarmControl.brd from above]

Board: 4 copper layers, 100.0 x 100.0 mm, 137 parts (0 on the bottom side), 83 nets.

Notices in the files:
parts and their libraries:
SparkFun-DiscreteSemi: Licensing: Creative Commons ShareAlike 4.0 International - https://creativecommons.org/licenses/by-sa/4.0
SparkFun-Resistors: Licensing: CC v3.0 Share-Alike You are welcome to use this library for commercial purposes.
rc-master-smd: Copyright (C) 2007, Bob Starr
